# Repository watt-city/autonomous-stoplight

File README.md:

# WATT City: Autonomous Stoplight

PCB design and firmware for the WATT City traffic light: an ESP32-S3 board that cycles green → yellow → red, switches to yellow → red when the pedestrian button is pressed, and broadcasts its state to cars over ESP-NOW.

**Owned by:** Stoplight team · **Leads:** Alisa Zhang, Katie Tao · **Questions:** `#watt-city` on WATT Slack

Part of [WATT City](https://github.com/watt-city), IEEE WATT's year-long project at UCLA. Related repos: [`autonomous-car`](https://github.com/watt-city/autonomous-car), [`camera`](https://github.com/watt-city/camera).

---

## Status

- ✅ PCB designed and fabricated
- ✅ Board powers up (Oct 2026)
- ⬜ Full bring-up: 3V3 rail and ripple, USB/LiPo switchover, LEDs, button (**Stoplight team: start here**)
- ⬜ Firmware: light cycle + pedestrian button
- ⬜ Firmware: ESP-NOW broadcast to cars

## Repo layout

```
hardware/
  watt_city_stoplight_pcb.kicad_pro   ← KiCad 10 project (open this)
  watt_city_stoplight_pcb.kicad_sch   ← top sheet → mcu / power / usb sub-sheets
  watt_city_stoplight_pcb.kicad_pcb   ← 2-layer layout
  production/                         ← what was sent to fab: Gerbers zip, BOM, positions (CPL), netlist
firmware/                             ← (to be created) one folder per Arduino sketch
```

## Board summary

| Block | Parts |
|---|---|
| MCU | ESP32-S3-WROOM-1-N8 (U301) |
| Power | 1S LiPo on JST-PH (J401) through slide switch (SW401), or USB-C 5 V, diode-ORed (D401/D402) into an AP2112K-3.3 LDO (U401) → 3V3. **No charger on the board:** charge the LiPo externally. |
| USB | USB-C (J201), 5.1 kΩ CC pull-downs (R201/R202), U201 (SLLC23T5V2U) on D+/D− |
| Buttons | Reset/EN (S301), BOOT/IO0 (S302), user button (S303) |
| Test points | GND, 3V3, USB, LiPo |

Full part list with LCSC numbers: [`hardware/production/bom.csv`](hardware/production/bom.csv).

### Firmware pin map

Read from the PCB netlist. Double-check against the schematic before relying on it.

| Function | GPIO | Notes |
|---|---|---|
| Red LED (D302) | **IO42** | 47 Ω series resistor (R304) |
| Yellow LED (D303) | **IO41** | 120 Ω series resistor (R306) |
| Green LED (D301) | **IO40** | 120 Ω series resistor (R305) |
| User / pedestrian button (S303) | **IO39** | 10 kΩ pull-up → **active LOW** (pressed = 0) |
| BOOT (S302) | IO0 | Hold while pressing reset to enter download mode |
| Reset (S301) | EN | |
| USB D− / D+ | IO19 / IO20 | Native USB, so set **USB CDC On Boot: Enabled** for Serial |

> ⚠️ **Check the red LED current before running it continuously.** With 47 Ω from 3.3 V and a ~2 V red LED, the current is roughly (3.3 − 2.0) / 47 ≈ 28 mA. That's above the ~20 mA typical for small LEDs and the ESP32-S3's recommended per-pin drive. Measure it on the first board, and consider a higher resistor value on the next revision.

## Bring-up checklist (first power-on)

1. **Visual inspection:** solder bridges on the ESP32 module and USB-C, LED and diode polarity.
2. **Resistance check:** measure 3V3 → GND and VBAT → GND with the board unpowered. Near 0 Ω means a short; stop.
3. **First power from a bench supply with a current limit** (~100 mA) before using a LiPo. Check 3V3 at TP105.
4. **USB:** plug in, confirm the board enumerates. If not, hold BOOT, tap RESET, release BOOT.
5. **Blink each LED** with a minimal sketch, then read the button.
6. **Log every test** in the hardware log (date, board #, setup, result, photos).

**LiPo safety:** never charge unattended, and stop using any battery that's puffy, hot, or damaged. Check polarity on the JST-PH lead before plugging in; some battery vendors wire it reversed.

## Firmware (to be written)

Set up the Arduino IDE with **esp32 by Espressif v3.x**, board `ESP32S3 Dev Module`, USB CDC On Boot **Enabled**.

The car expects this ESP-NOW packet, defined in [`autonomous-car/firmware/main_board/watt_link.h`](https://github.com/watt-city/autonomous-car/blob/main/firmware/main_board/watt_link.h):

```c
enum LightState : uint8_t { LIGHT_RED = 0, LIGHT_YELLOW = 1, LIGHT_GREEN = 2, LIGHT_UNKNOWN = 3 };

struct __attribute__((packed)) V2XPacket {
  uint8_t intersectionId;   // must equal the AprilTag ID placed at this intersection
  uint8_t lightState;       // LightState
  uint8_t secondsToChange;  // countdown hint, 0 if unknown
};
```

Copy `watt_link.h` into your sketch folder rather than redefining the struct, so both sides stay identical. Changes to the format need agreement from the Car and Camera teams.

## Editing the PCB

- KiCad **10** or newer is required to open the project.
- **Only one person edits at a time.** Claim it in `#watt-city` on Slack first; KiCad files don't merge.
- Before the next fab: bump the board revision text on the silkscreen, regenerate `production/`, then **tag** the commit (e.g. `stoplight-hw-v2.0`) and attach the Gerbers to a GitHub Release.
- `main` is the LDO design, and `production/` holds its fab files. The earlier buck-boost version (TPS63070) is saved as the tag `archive/buck_version` (Aug 2; KiCad files and production files at the repo root, from before the `hardware/` folder existed). `c3fc9c1` switched back to the LDO.

## Contributing

Read [CONTRIBUTING.md](CONTRIBUTING.md) before your first push. In short: pull before you start, push when you finish; push straight to `main` for `hardware/` (after claiming it) and docs; **use a branch + pull request for anything in `firmware/`**; log every hardware test in the hardware log.

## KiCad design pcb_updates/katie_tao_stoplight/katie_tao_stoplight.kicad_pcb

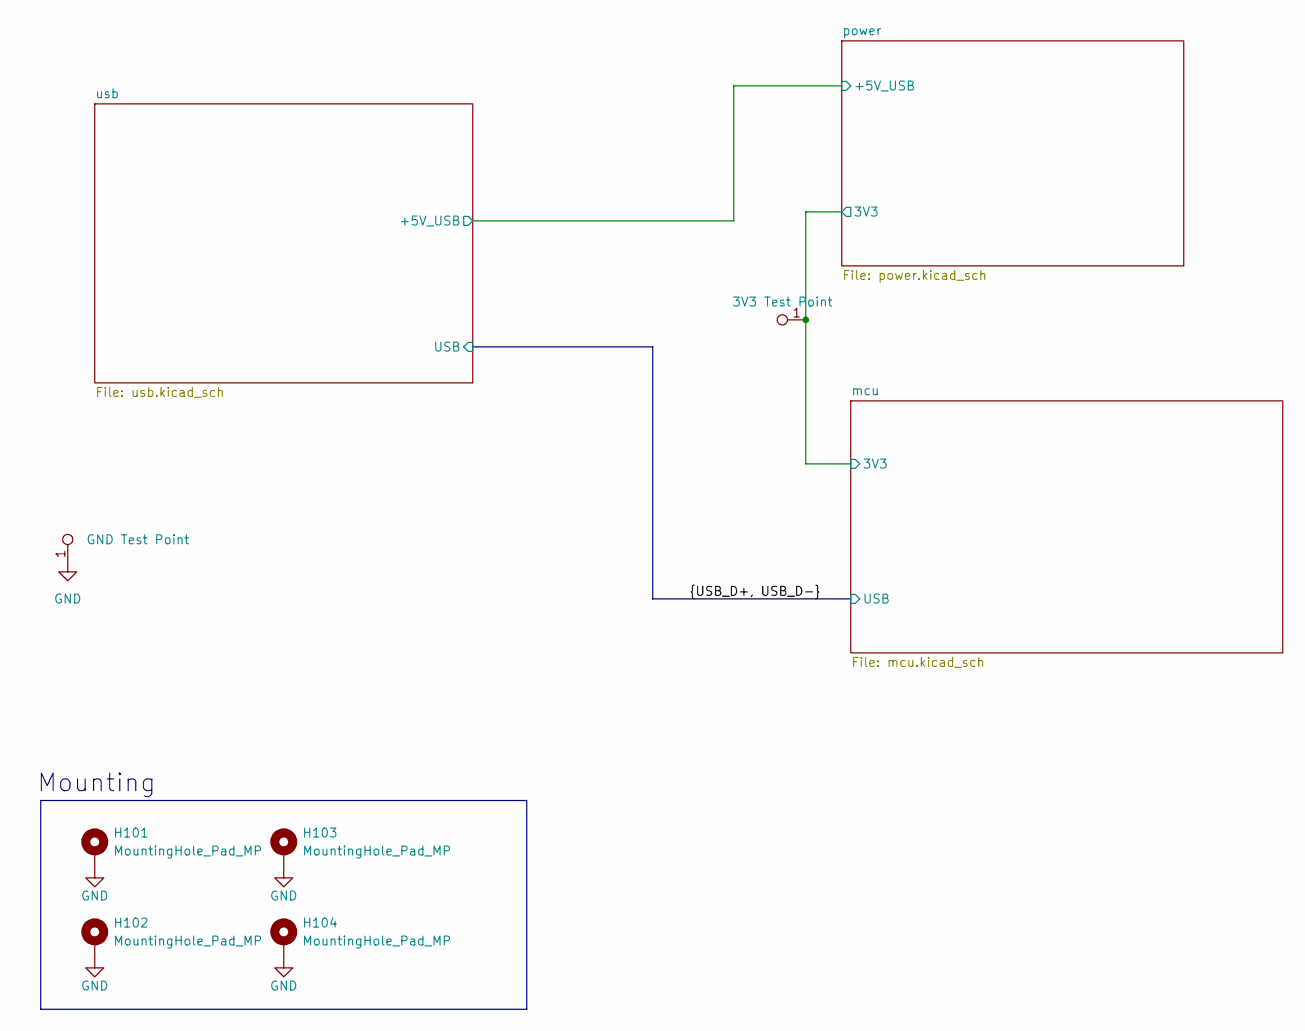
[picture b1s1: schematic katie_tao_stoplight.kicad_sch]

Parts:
H101, H102, H103, H104: MountingHole_Pad_MP; MountingHole_2.7mm_M2.5_Pad_Via; Mouser P/N N/A; Digikey P/N N/A
TP101: GND Test Point; TestPoint_Keystone_5019_Miniature; Manufacturer P/N RH-5019; Digikey P/N 36-5019CT-ND
TP105: 3V3 Test Point; TestPoint_Keystone_5019_Miniature; Manufacturer P/N RH-5019; Digikey P/N 36-5019CT-ND

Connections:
/mcu/3V3: TP105.1; also elsewhere on the board
GND: H101.1 (1_1), H102.1 (1_1), H103.1 (1_1), H104.1 (1_1), TP101.1; also elsewhere on the board

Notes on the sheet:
Mounting

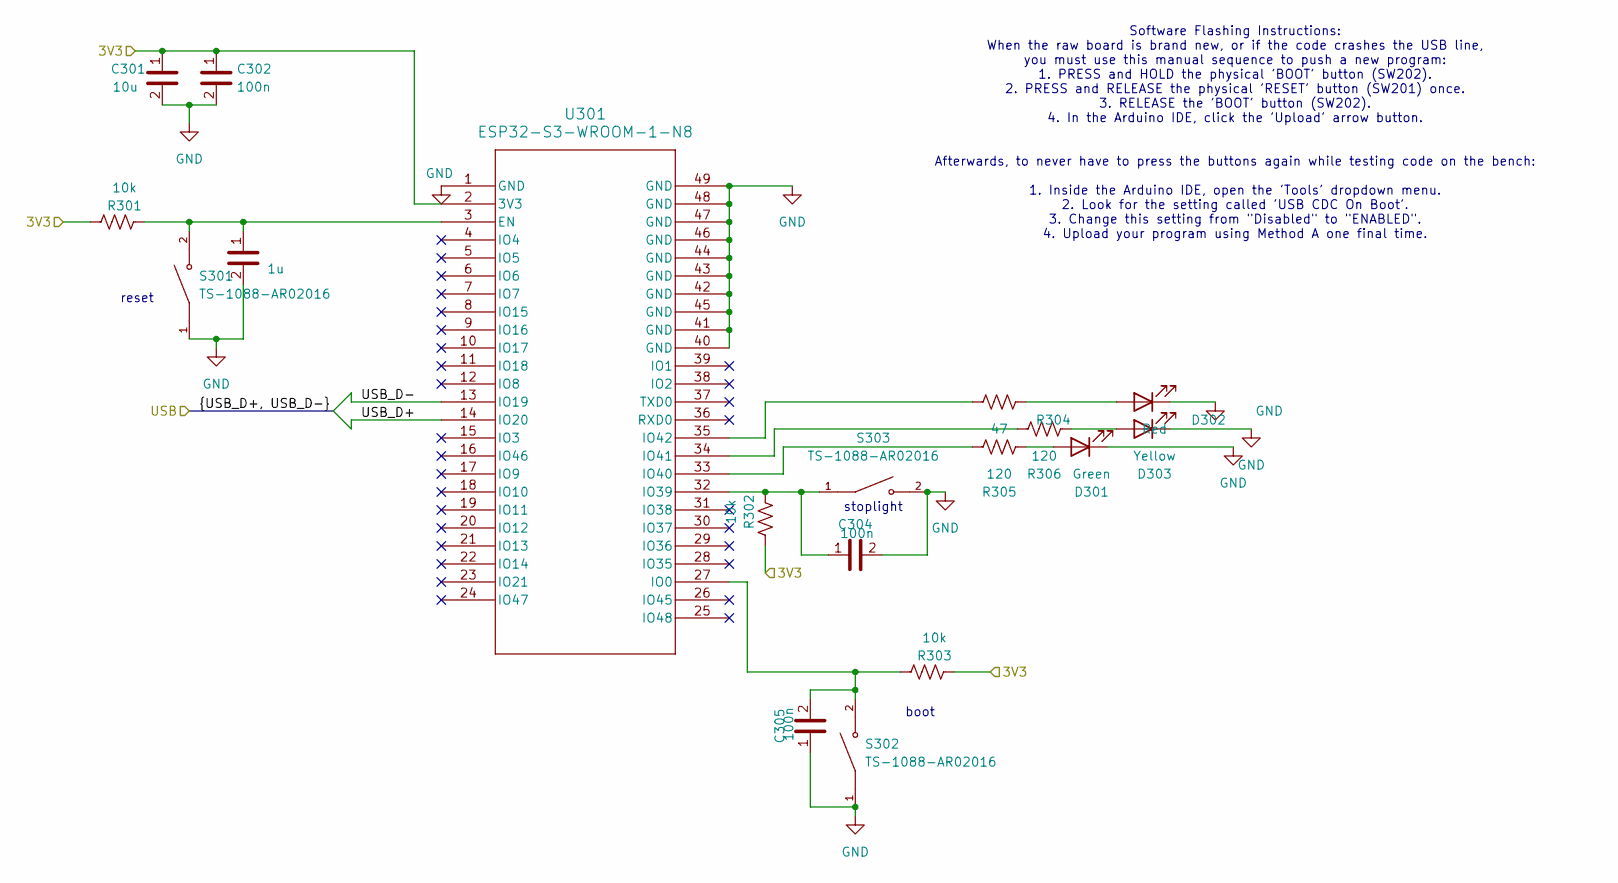
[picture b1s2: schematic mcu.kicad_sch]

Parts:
C301: 10u; C_0603_1608Metric_Pad1.08x0.95mm_HandSolder; LCSC P/N C19702
C302, C304, C305: 100n; C_0603_1608Metric_Pad1.08x0.95mm_HandSolder; Mouser P/N 581-06035C104KAT2A; Digikey P/N 478-KGM15BR71H104KTCT-ND
C303: 1u; C_0603_1608Metric_Pad1.08x0.95mm_HandSolder; LCSC P/N C15849
D301: Green; D_0805_2012Metric_Pad1.15x1.40mm_HandSolder; Mouser P/N 755-SMLMN2ECTT86C; Digikey P/N 846-SMLMN2ECTT86CCT-ND
D302: Red; D_0603_1608Metric_Pad1.05x0.95mm_HandSolder; Mouser P/N 720-LRQ976.01; Digikey P/N 475-LRQ976.01-P2R2-1CT-ND
D303: Yellow; D_0805_2012Metric_Pad1.15x1.40mm_HandSolder; Mouser P/N 645-599-0140-007F; Digikey P/N 350-4356-1-ND
R301, R302, R303: 10k; R_0603_1608Metric_Pad0.98x0.95mm_HandSolder; Mouser P/N 708-RMCF0603FT10K0; Digikey P/N RMCF0603FT10K0CT-ND
R304: 47; R_0805_2012Metric_Pad1.20x1.40mm_HandSolder; Mouser P/N 708-RMCF0805FT47R0; Digikey P/N RMCF0805FT47R0CT-ND
R305, R306: 120; R_0805_2012Metric_Pad1.20x1.40mm_HandSolder; Mouser P/N 708-RMCF0805FT120R; Digikey P/N RMCF0805FT120RCT-ND
S301, S302, S303: TS-1088-AR02016; SW_TS-1088-AR02016; PARTREV N/A
U301: ESP32-S3-WROOM-1-N8; ESP32-S3-WROOM-1_EXP

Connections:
/USB_D+: U301.14 (IO20); also elsewhere on the board
/USB_D-: U301.13 (IO19); also elsewhere on the board
/mcu/3V3: C301.1, C302.1, R301.1, R302.1, R303.2, U301.2 (3V3); also elsewhere on the board
GND: C301.2, C302.2, C303.2, C304.2, C305.1, D301.1 (K), D302.1 (K), D303.1 (K), S301.1, S302.1, S303.2, U301.1 (GND), U301.40 (GND), U301.41 (GND), U301.42 (GND), U301.43 (GND), U301.44 (GND), U301.45 (GND), U301.46 (GND), U301.47 (GND), U301.48 (GND), U301.49 (GND); also elsewhere on the board
unnamed: D301.2 (A), R305.1
unnamed: D302.2 (A), R304.1
unnamed: D303.2 (A), R306.1
unnamed: C303.1, R301.2, S301.2, U301.3 (EN)
unnamed: C305.2, R303.1, S302.2, U301.27 (IO0)
unnamed: C304.1, R302.2, S303.1, U301.32 (IO39)
unnamed: R305.2, U301.33 (IO40)
unnamed: R306.2, U301.34 (IO41)
unnamed: R304.2, U301.35 (IO42)

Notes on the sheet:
reset
Software Flashing Instructions: When the raw board is brand new, or if the code crashes the USB line, you must use this manual sequence to push a new program: 1. PRESS and HOLD the physical 'BOOT' button (SW202). 2. PRESS and RELEASE the physical 'RESET' button (SW201) once. 3. RELEASE the 'BOOT' b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
boot
stoplight

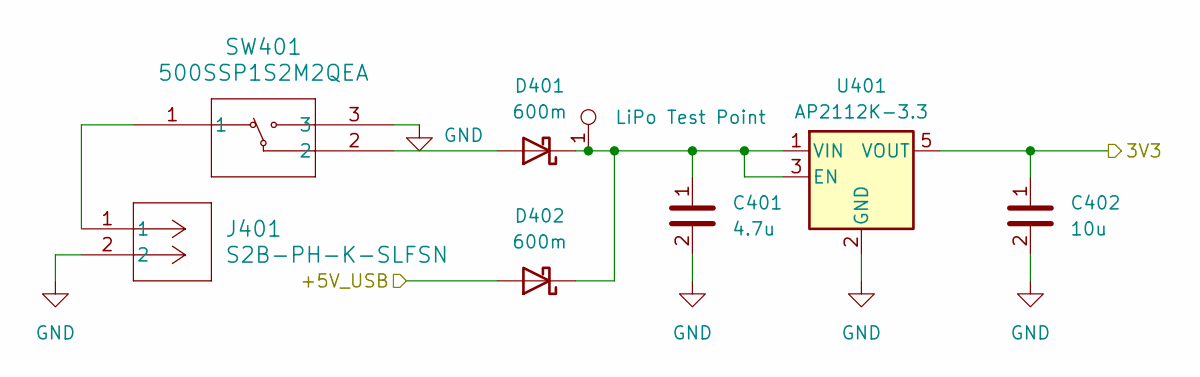
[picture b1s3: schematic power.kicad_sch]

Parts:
C401: 4.7u; C_0805_2012Metric_Pad1.18x1.45mm_HandSolder; Mouser P/N 581-KGM21AR51A475KU; Digikey P/N 478-KGM21AR51A475KUCT-ND
C402: 10u; C_0603_1608Metric_Pad1.08x0.95mm_HandSolder; LCSC P/N C19702
D401, D402: 600m; D_SOD-323_HandSoldering; Mouser P/N 833-B5819WS-TP; LCSC P/N C191023
J401: S2B-PH-K-SLFSN; CONN_S2B-PH-K-S_JST
SW401: 500SSP1S2M2QEA; 500SSP1_EWI
TP401: LiPo Test Point; TestPoint_Keystone_5019_Miniature; Manufacturer P/N RH-5019; Digikey P/N 36-5019CT-ND
U401: AP2112K-3.3; SOT-23-5

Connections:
/mcu/3V3: C402.1, U401.5 (VOUT); also elsewhere on the board
/power/+5V_USB: D402.2 (A); also elsewhere on the board
GND: C401.2, C402.2, J401.2, SW401.3, U401.2 (GND); also elsewhere on the board
unnamed: D401.2 (A), SW401.2
unnamed: C401.1, D401.1 (K), D402.1 (K), TP401.1, U401.1 (VIN), U401.3 (EN)
unnamed: J401.1, SW401.1

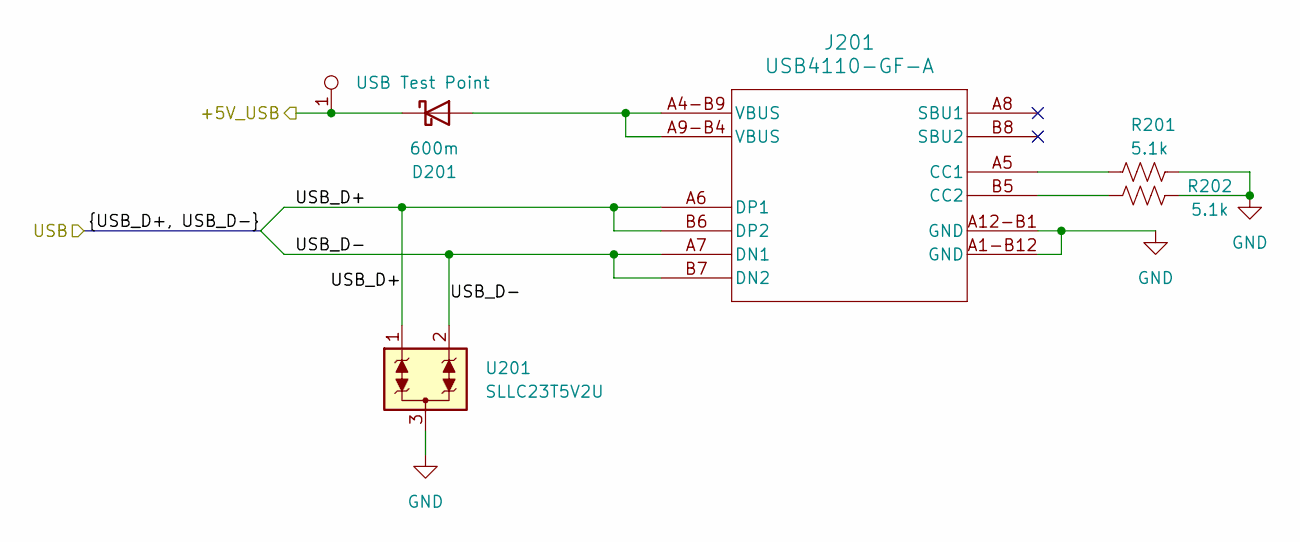
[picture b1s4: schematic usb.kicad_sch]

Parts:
D201: 600m; D_SOD-323_HandSoldering; Mouser P/N 833-B5819WS-TP; LCSC P/N C191023
J201: USB4110-GF-A; USB4110-GF-A_GCT
R201, R202: 5.1k; R_0805_2012Metric_Pad1.20x1.40mm_HandSolder; Mouser P/N 708-RMCF0805FT5K10; Digikey P/N RMCF0805FT5K10CT-ND
TP201: USB Test Point; TestPoint_Keystone_5019_Miniature; Manufacturer P/N RH-5019; Digikey P/N 36-5019CT-ND
U201: SLLC23T5V2U; SOT-23; Manufacturer P/N SLLC23T5V2U; Digikey P/N 5399-SLLC23T5V2UCT-ND

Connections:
/USB_D+: J201.A6 (DP1), J201.B6 (DP2), U201.1; also elsewhere on the board
/USB_D-: J201.A7 (DN1), J201.B7 (DN2), U201.2; also elsewhere on the board
/power/+5V_USB: D201.1 (K), TP201.1; also elsewhere on the board
GND: J201.A1-B12 (GND), J201.A12-B1 (GND), R201.1, R202.1, U201.3; also elsewhere on the board
unnamed: D201.2 (A), J201.A4-B9 (VBUS), J201.A9-B4 (VBUS)
unnamed: J201.A5 (CC1), R201.2
unnamed: J201.B5 (CC2), R202.2

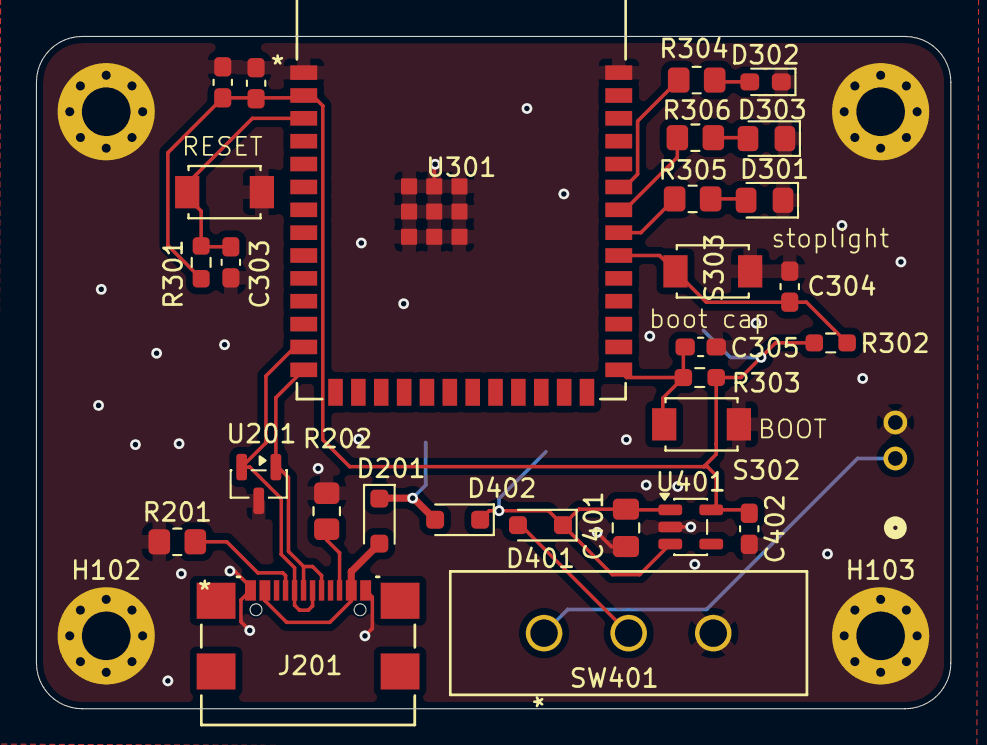
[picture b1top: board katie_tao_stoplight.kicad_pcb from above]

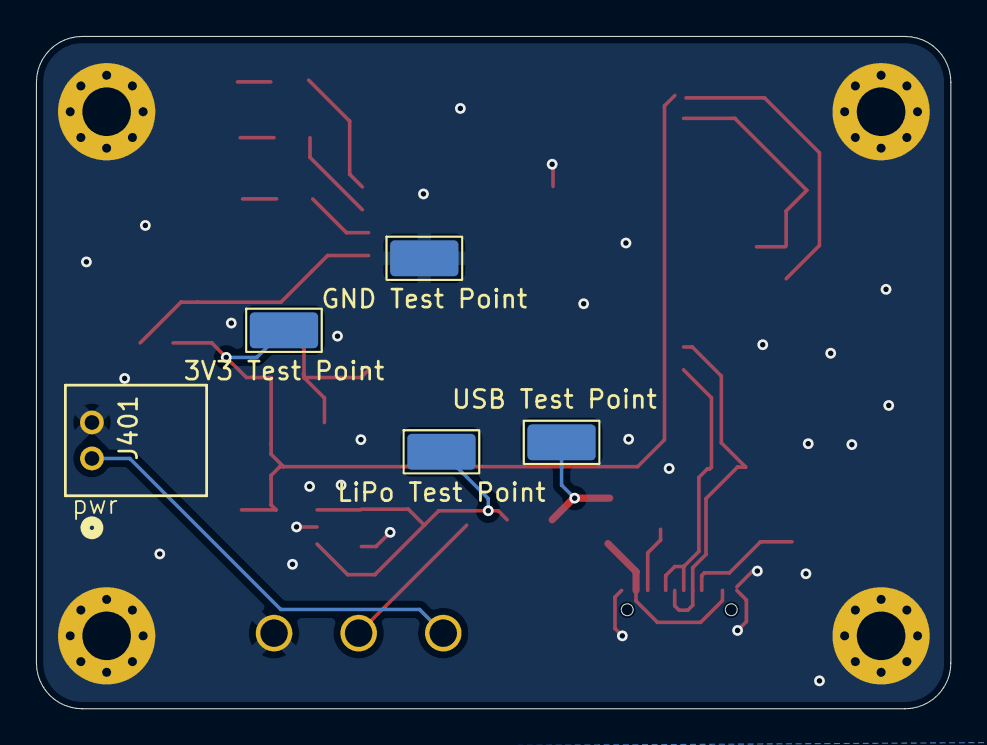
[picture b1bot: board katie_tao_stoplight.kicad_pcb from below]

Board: 2 copper layers, 50.8 x 37.3 mm, 38 parts (5 on the bottom side), 20 nets.
